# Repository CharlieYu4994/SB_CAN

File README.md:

# SB_CAN (StealthBurner_CAN)
为 Voron Design 的 StealthBurner 设计的工具头 PCB 板

## 特点
+ 使用 StealthBurner 官方的固定孔位，可以无损兼容现有打印件
+ 使用 CAN 总线与主控制器通讯，可靠性更好
+ 板载 ADXL345，无需另外安装加速度计就可以做共振补偿
+ 板载 MAX31865，可以使用二/三/四线制 PT100 温度传感器
+ 板载 TMP235，可以做仓温监控
+ 板载三路四线风扇接口，可以监控风扇转速
+ 预留线性霍尔提供耗材直径检测
+ 预留一路 I2C 接口，可以使用 LDC1612 IDM 传感器

## 使用

### 打样
使用各文件夹内的「SB-**-board.zip」文件即可，建议使用 1.6mm 板厚，4mil 最小线宽

### 接线 (均为从左向右)

+ FAN2 (风扇2)
  + +24V
  + GPIO14
  + GPIO15
  + GND
+ FS (耗材传感器)
  + +3.3V
  + GPI16
  + ADC0
  + GND
+ LDC (LDC1612)
  + GND
  + GPIO8
  + GPIO7
  + +5V
+ PT100
  + FORCE-
  + RTDIN-
  + RTDIN+
  + FORCE+
+ HS (上下)
  + GND (GPIO17)
  + +24V

+ STEP (步进电机)
  + A-
  + A+
  + B+
  + B-

+ FAN1 (风扇1)
  + +12V
  + GPIO13
  + GPIO11
  + GND
+ NEO (WS2812 LED)
  + GND
  + GPIO9
  + +3.7V
+ FAN0 (风扇0)
  + GND
  + GPIO12
  + GPIO10
  + +12V

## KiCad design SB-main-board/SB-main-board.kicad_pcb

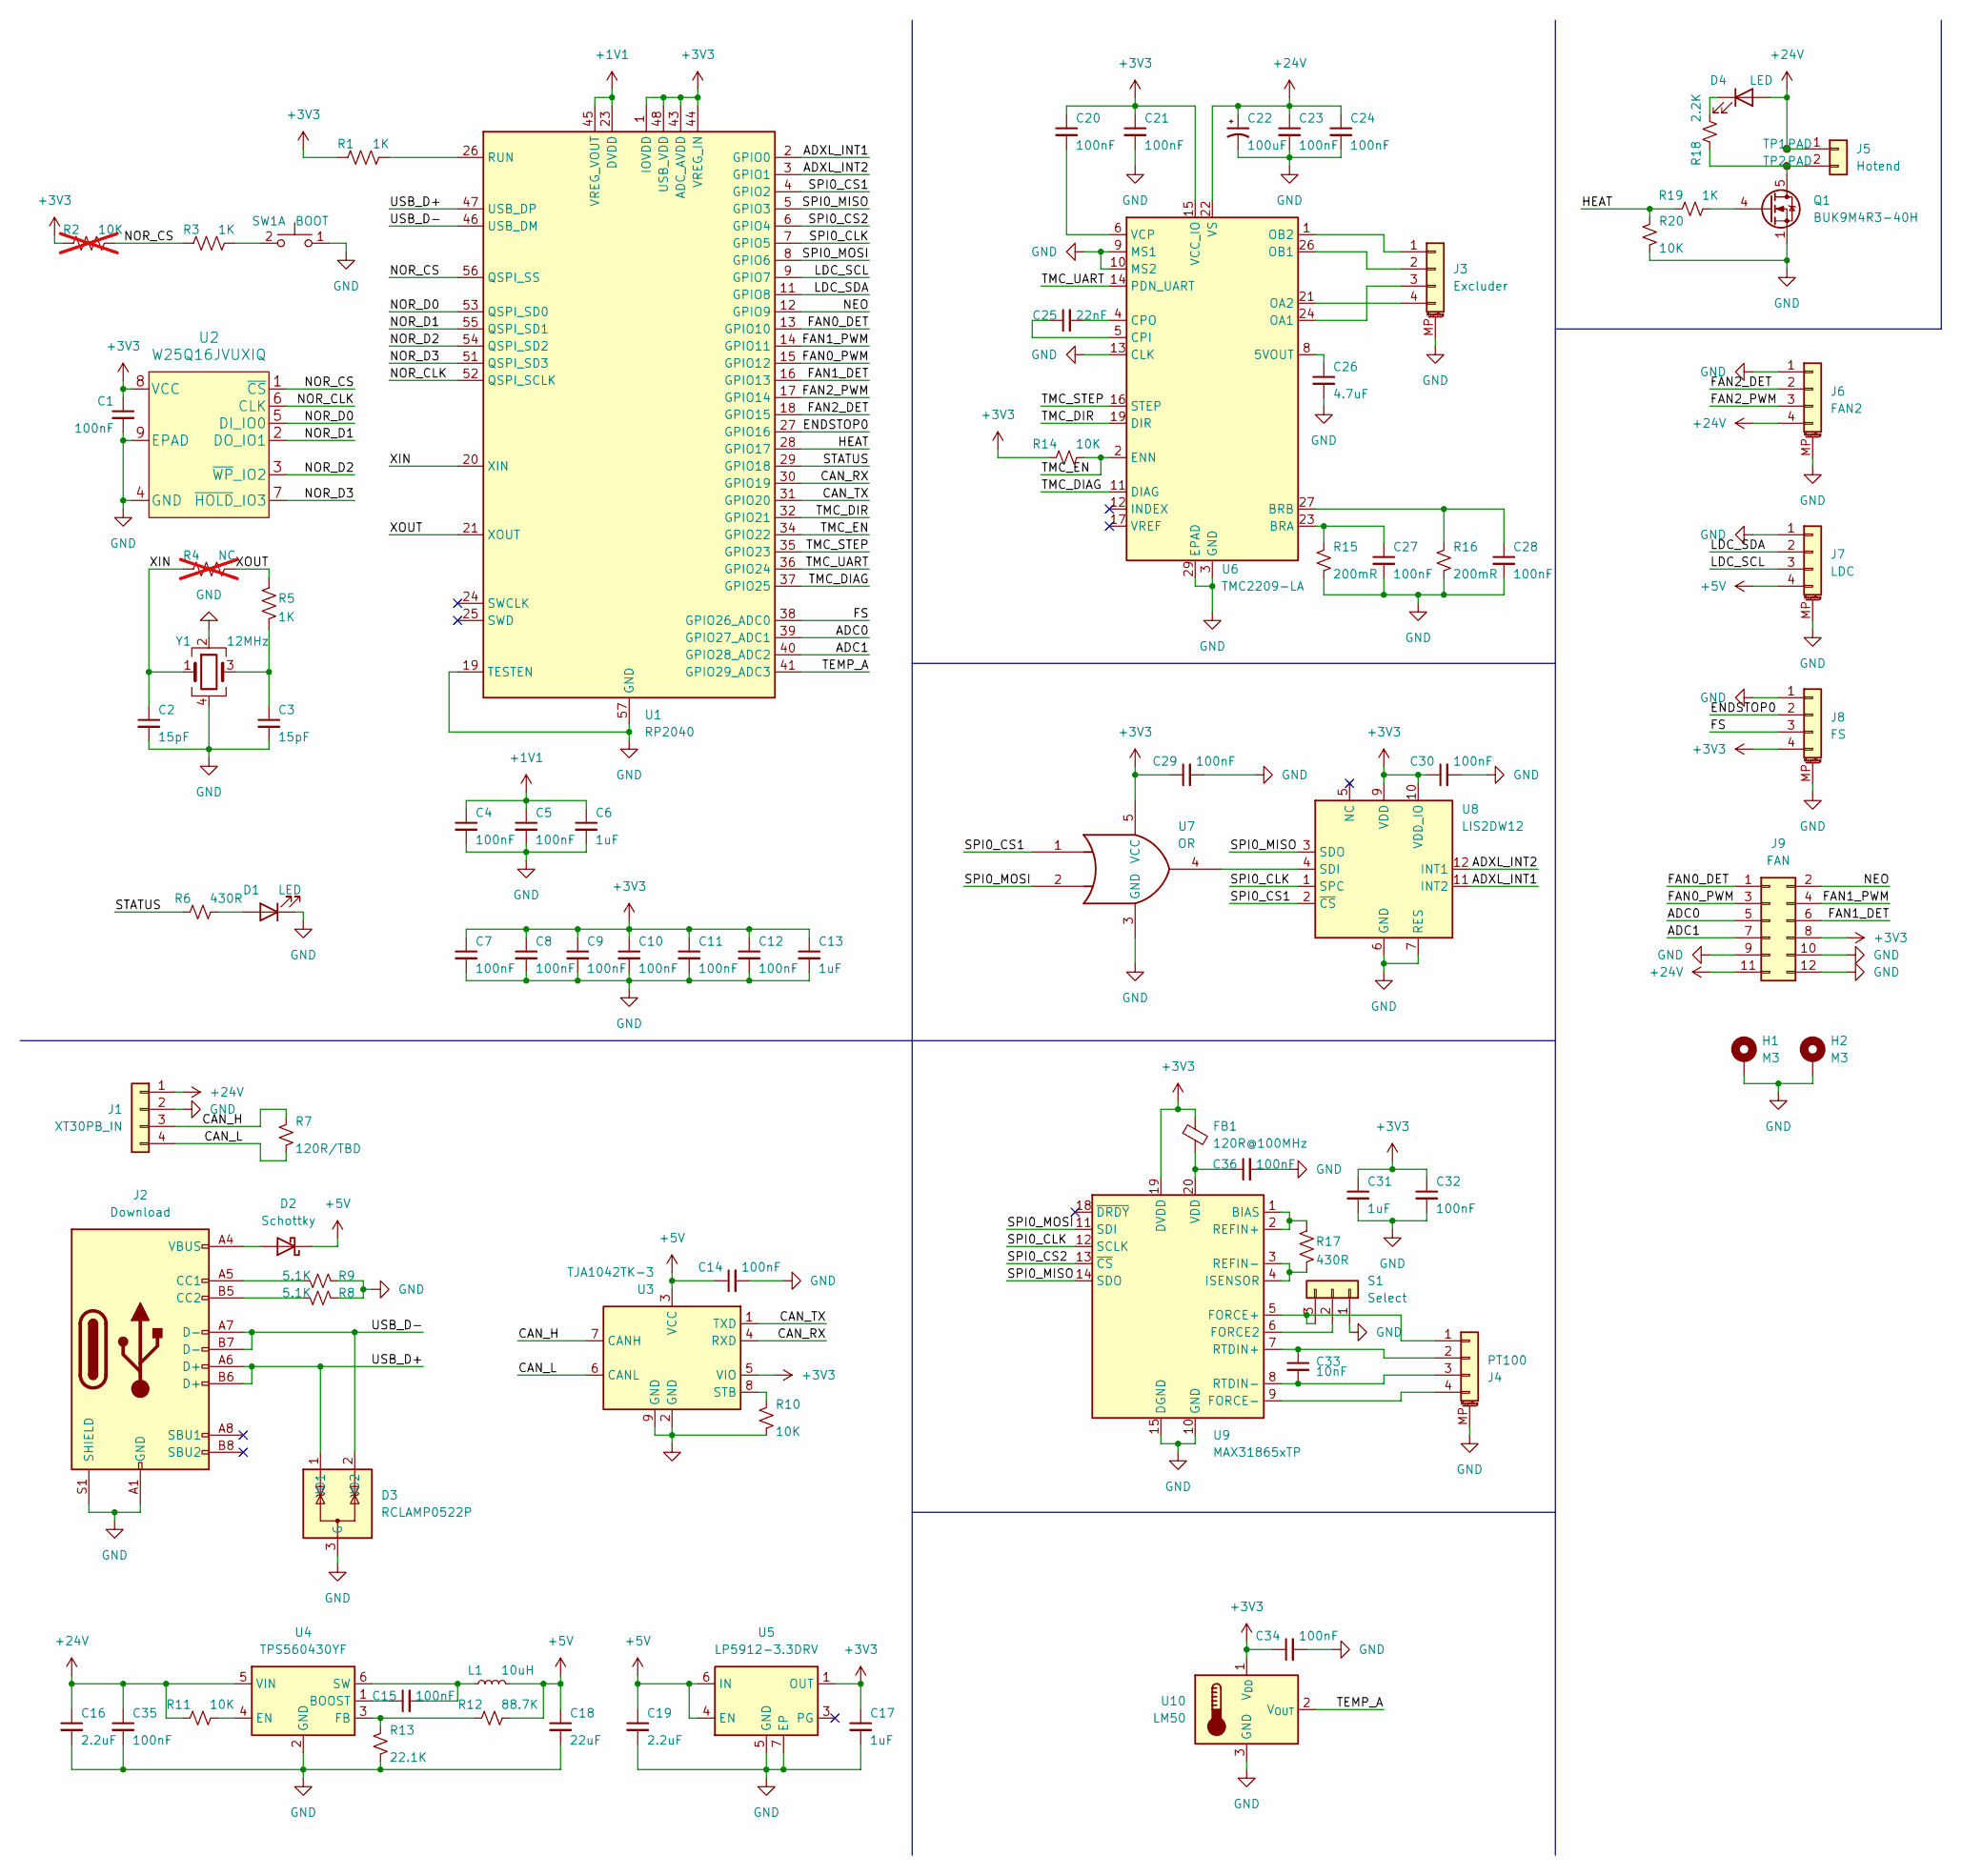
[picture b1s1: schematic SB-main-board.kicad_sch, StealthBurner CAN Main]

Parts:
C1, C4, C5, C7, C8, C9, C10, C11, C12, C14, C15, C20, C21, C23, C24, C27, C28, C29, C30, C32, C34, C35, C36: 100nF; C_0402_1005Metric
C2, C3: 15pF; C_0402_1005Metric
C6, C13, C31: 1uF; C_0402_1005Metric
C16: 2.2uF; C_1206_3216Metric
C17: 1uF; C_0603_1608Metric
C18: 22uF; C_0805_2012Metric
C19: 2.2uF; C_0603_1608Metric
C22: 100uF; CP_Elec_6.3x7.7
C25: 22nF; C_0402_1005Metric
C26: 4.7uF; C_0805_2012Metric
C33: 10nF; C_0402_1005Metric
D1, D4: LED; LED_0402_1005Metric
D2: Schottky; D_SOD-882D
D3: RCLAMP0522P; SLP1610P4
FB1: 120R@100MHz; L_0603_1608Metric
H1, H2: M3; MountingHole_3.2mm_M3_ISO14580_Pad
J1: XT30PB_IN; AMASS_XT30PW-M_1x02_P2.50mm_Horizontal
J2: Download; USB_C_Receptacle_GCT_USB4105-xx-A_16P_TopMnt_Horizontal
J3: Excluder; JST_PH_B4B-PH-SM4-TB_1x04-1MP_P2.00mm_Vertical
J4: PT100; Molex_PicoBlade_53261-0471_1x04-1MP_P1.25mm_Horizontal
J5: Hotend; Molex_Micro-Fit_3.0_43045-0200_2x01_P3.00mm_Horizontal
J6: FAN2; Molex_PicoBlade_53398-0471_1x04-1MP_P1.25mm_Vertical
J7: LDC; Molex_PicoBlade_53261-0471_1x04-1MP_P1.25mm_Horizontal
J8: FS; Molex_PicoBlade_53398-0471_1x04-1MP_P1.25mm_Vertical
J9: FAN; PinHeader_2x06_P2.00mm_Horizontal
L1: 10uH; L_Changjiang_FTC303020D
Q1: BUK9M4R3-40H; LFPAK33
R1, R3, R5, R19: 1K; R_0402_1005Metric
R2: 10K; R_0402_1005Metric; not fitted
R4: NC; R_0402_1005Metric; not fitted
R6: 430R; R_0402_1005Metric
R7: 120R/TBD; R_0805_2012Metric
R8, R9: 5.1K; R_0402_1005Metric
R10, R11, R14, R20: 10K; R_0402_1005Metric
R12: 88.7K; R_0402_1005Metric
R13: 22.1K; R_0402_1005Metric
R15, R16: 200mR; R_0805_2012Metric
R17: 430R; R_0603_1608Metric
R18: 2.2K; R_0402_1005Metric
S1: Select
SW1: BOOT; Panasonic_EVQPUJ_EVQPUA
TP1, TP2: PAD
U1: RP2040; QFN-56-1EP_7x7mm_P0.4mm_EP3.2x3.2mm
U2: W25Q16JVUXIQ; USON-8_2.0x3.0mm_P0.5mm
U3: TJA1042TK-3; DFN-8-1EP_3x3mm_P0.65mm_EP1.55x2.4mm
U4: TPS560430YF; SOT-23-6
U5: LP5912-3.3DRV; WSON-6-1EP_2x2mm_P0.65mm_EP1x1.6mm
U6: TMC2209-LA; QFN-28-1EP_5x5mm_P0.5mm_EP3.75x3.75mm
U7: OR; SOT-353_SC-70-5
U8: LIS2DW12; LGA-12_2x2mm_P0.5mm
U9: MAX31865xTP; TQFN-20-1EP_5x5mm_P0.65mm_EP3.25x3.25mm
U10: LM50; SOT-23
Y1: 12MHz; Crystal_SMD_2520-4Pin_2.5x2.0mm

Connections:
+1V1: C4.1, C5.1, C6.1, U1.23 (DVDD), U1.45 (VREG_VOUT), U1.50 (DVDD)
+3V3: C1.1, C7.1, C8.1, C9.1, C10.1, C11.1, C12.1, C13.1, C17.1, C20.1, C21.1, C29.1, C30.1, C31.1, C32.1, C34.1, FB1.1, J8.4, J9.8, R1.1, R2.1, R14.1, U1.1 (IOVDD), U1.10 (IOVDD), U1.22 (IOVDD), U1.33 (IOVDD), U1.42 (IOVDD), U1.43 (ADC_AVDD), U1.44 (VREG_IN), U1.48 (USB_VDD), U1.49 (IOVDD), U2.8 (VCC), U3.5 (VIO), U5.1 (OUT), U6.15 (VCC_IO), U7.5 (VCC), U8.9 (VDD), U8.10 (VDD_IO), U9.19 (DVDD), U10.1 (V_{DD})
+5V: C14.1, C18.1, C19.1, D2.1 (K), J7.4, L1.2, R12.2, U3.3 (VCC), U5.4 (EN), U5.6 (IN)
+24V: C16.1, C22.1, C23.1, C24.1, C35.1, D4.2 (A), J1.1, J5.1, J6.4, J9.11, R11.1, TP1.1, U4.5 (VIN), U6.22 (VS), U6.28 (VS)
/ADC0: J9.5, U1.39 (GPIO27_ADC1)
/ADC1: J9.7, U1.40 (GPIO28_ADC2)
/ADXL_INT1: U1.2 (GPIO0), U8.11 (INT2)
/ADXL_INT2: U1.3 (GPIO1), U8.12 (INT1)
/CAN_H: J1.3, R7.1, U3.7 (CANH)
/CAN_L: J1.4, R7.2, U3.6 (CANL)
/CAN_RX: U1.30 (GPIO19), U3.4 (RXD)
/CAN_TX: U1.31 (GPIO20), U3.1 (TXD)
/ENDSTOP0: J8.2, U1.27 (GPIO16)
/FAN0_DET: J9.1, U1.13 (GPIO10)
/FAN0_PWM: J9.3, U1.15 (GPIO12)
/FAN1_DET: J9.6, U1.16 (GPIO13)
/FAN1_PWM: J9.4, U1.14 (GPIO11)
/FAN2_DET: J6.2, U1.18 (GPIO15)
/FAN2_PWM: J6.3, U1.17 (GPIO14)
/FS: J8.3, U1.38 (GPIO26_ADC0)
/HEAT: R19.1, R20.1, U1.28 (GPIO17)
/LDC_SCL: J7.3, U1.9 (GPIO7)
/LDC_SDA: J7.2, U1.11 (GPIO8)
/NEO: J9.2, U1.12 (GPIO9)
/NOR_CLK: U1.52 (QSPI_SCLK), U2.6 (CLK)
/NOR_CS: R2.2, R3.1, U1.56 (QSPI_SS), U2.1 (~CS)
/NOR_D0: U1.53 (QSPI_SD0), U2.5 (DI_IO0)
/NOR_D1: U1.55 (QSPI_SD1), U2.2 (DO_IO1)
/NOR_D2: U1.54 (QSPI_SD2), U2.3 (~WP_IO2)
/NOR_D3: U1.51 (QSPI_SD3), U2.7 (~HOLD_IO3)
/SPI0_CLK: U1.7 (GPIO5), U8.1 (SPC), U9.12 (SCLK)
/SPI0_CS1: U1.4 (GPIO2), U7.1, U8.2 (~CS)
/SPI0_CS2: U1.6 (GPIO4), U9.13 (~CS)
/SPI0_MISO: U1.5 (GPIO3), U8.3 (SDO), U9.14 (SDO)
/SPI0_MOSI: U1.8 (GPIO6), U7.2, U9.11 (SDI)
/STATUS: R6.1, U1.29 (GPIO18)
/TEMP_A: U1.41 (GPIO29_ADC3), U10.2 (V_{OUT})
/TMC_DIAG: U1.37 (GPIO25), U6.11 (DIAG)
/TMC_DIR: U1.32 (GPIO21), U6.19 (DIR)
/TMC_EN: R14.2, U1.34 (GPIO22), U6.2 (ENN)
/TMC_STEP: U1.35 (GPIO23), U6.16 (STEP)
/TMC_UART: U1.36 (GPIO24), U6.14 (PDN_UART)
/USB_D+: D3.1 (IO1), D3.6 (NC), J2.A6 (D+), J2.B6 (D+), U1.47 (USB_DP)
/USB_D-: D3.2 (IO2), D3.5 (NC), J2.A7 (D-), J2.B7 (D-), U1.46 (USB_DM)
/XIN: C2.1, R4.1, U1.20 (XIN), Y1.1
/XOUT: R4.2, R5.2, U1.21 (XOUT)
GND: C1.2, C2.2, C3.2, C4.2, C5.2, C6.2, C7.2, C8.2, C9.2, C10.2, C11.2, C12.2, C13.2, C14.2, C16.2, C17.2, C18.2, C19.2, C21.2, C22.2, C23.2, C24.2, C26.2, C27.2, C28.2, C29.2, C30.2, C31.2, C32.2, C34.2, C35.2, C36.2, D1.1 (K), D3.3 (G), D3.4 (G), H1.1, H2.1, J1.2, J2.A1 (GND), J2.A12 (GND), J2.B1 (GND), J2.B12 (GND), J2.S1 (SHIELD), J3.MP (MountPin), J4.MP (MountPin), J6.1, J6.MP (MountPin), J7.1, J7.MP (MountPin), J8.1, J8.MP (MountPin), J9.9, J9.10, J9.12, Q1.1 (S), Q1.2 (S), Q1.3 (S), R8.1, R9.1, R10.2, R13.2, R15.2, R16.2, R20.2, S1.1, SW1.1 (C), U1.19 (TESTEN), U1.57 (GND), U2.4 (GND), U2.9 (EPAD), U3.2 (GND), U3.9 (GND), U4.2 (GND), U5.5 (GND), U5.7 (EP), U6.3 (GND), U6.9 (MS1), U6.10 (MS2), U6.13 (CLK), U6.18 (GND), U6.29 (EPAD), U7.3 (GND), U8.6 (GND), U8.7 (RES), U8.8 (GND), U9.10 (GND), U9.15 (DGND), U9.16 (GND), U9.21 (GND), U10.3 (GND), Y1.2, Y1.4
unnamed: C3.1, R5.1, Y1.3
unnamed: D1.2 (A), R6.2
unnamed: D2.2 (A), J2.A4 (VBUS), J2.A9 (VBUS), J2.B4 (VBUS), J2.B9 (VBUS)
unnamed: D4.1 (K), R18.2
unnamed: J2.A5 (CC1), R9.2
unnamed: J2.B5 (CC2), R8.2
unnamed: J3.1, U6.1 (OB2)
unnamed: J3.2, U6.26 (OB1)
unnamed: J3.3, U6.24 (OA1)
unnamed: J3.4, U6.21 (OA2)
unnamed: J4.1, S1.3, U9.5 (FORCE+)
unnamed: C33.1, J4.2, U9.7 (RTDIN+)
unnamed: C33.2, J4.3, U9.8 (RTDIN-)
unnamed: J4.4, U9.9 (FORCE-)
unnamed: J5.2, Q1.5 (D), R18.1, TP2.1
unnamed: Q1.4 (G), R19.2
unnamed: S1.2, U9.6 (FORCE2)
unnamed: R3.2, SW1.2 (D)
unnamed: R1.2, U1.26 (RUN)
unnamed: R10.1, U3.8 (STB)
unnamed: C15.1, U4.1 (BOOST)
unnamed: R11.2, U4.4 (EN)
unnamed: R12.1, R13.1, U4.3 (FB)
unnamed: C15.2, L1.1, U4.6 (SW)
unnamed: C26.1, U6.8 (5VOUT)
unnamed: C27.1, R15.1, U6.23 (BRA)
unnamed: C28.1, R16.1, U6.27 (BRB)
unnamed: C25.1, U6.5 (CPI)
unnamed: C25.2, U6.4 (CPO)
unnamed: C20.2, U6.6 (VCP)
unnamed: U7.4, U8.4 (SDI)
unnamed: R17.2, U9.1 (BIAS), U9.2 (REFIN+)
unnamed: R17.1, U9.3 (REFIN-), U9.4 (ISENSOR)
unnamed: C36.1, FB1.2, U9.20 (VDD)

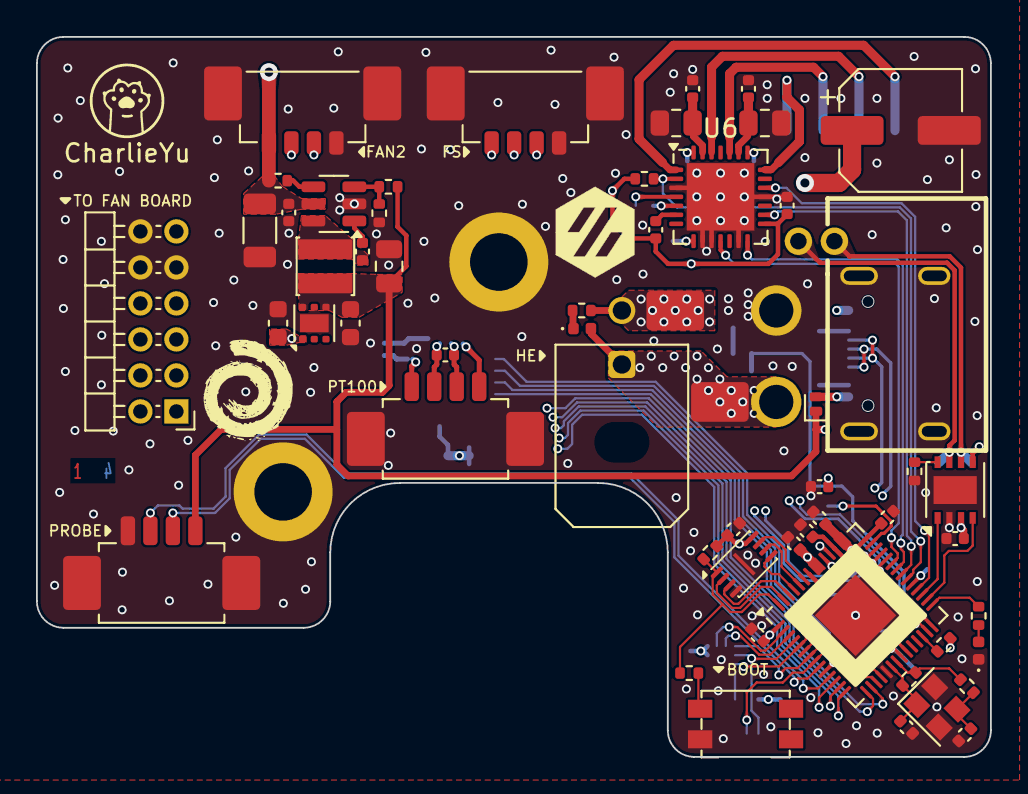
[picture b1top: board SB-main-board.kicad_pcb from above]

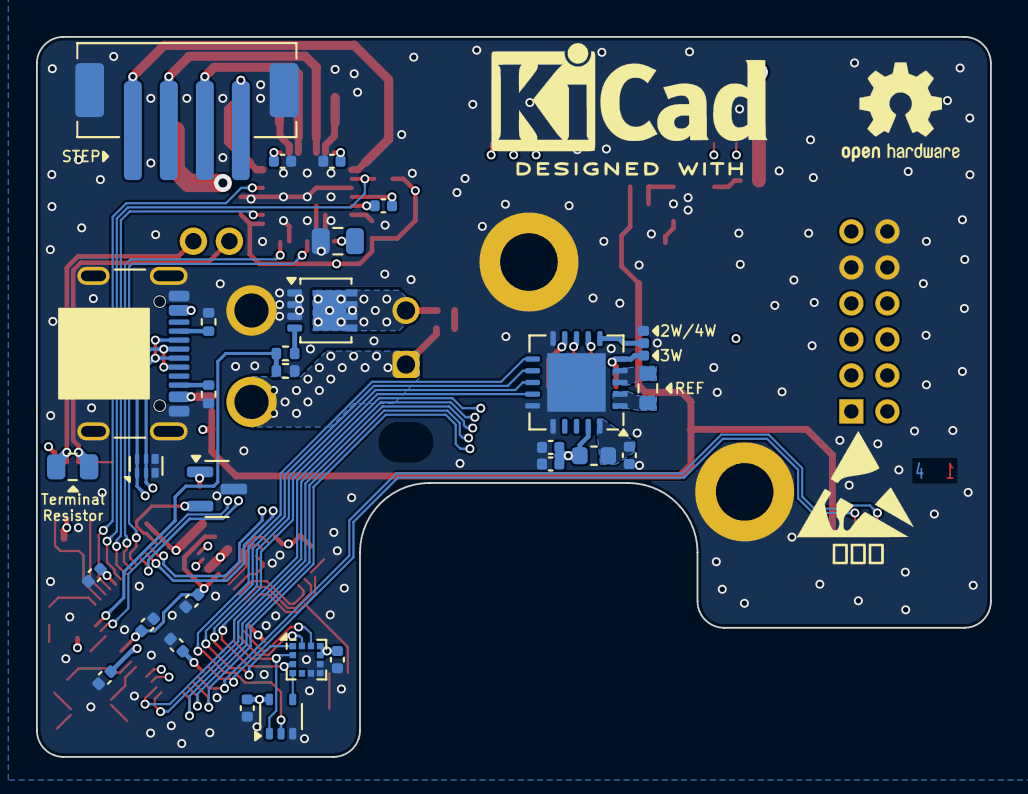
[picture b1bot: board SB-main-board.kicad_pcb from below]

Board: 4 copper layers, 53.0 x 40.0 mm, 95 parts (33 on the bottom side), 81 nets.

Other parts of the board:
G1: CharlieYu; charlieyu
G2: LOGO; Progynova
G3: Voron Hex; Voron_Logo_Hex
G4: KiCad-Logo2_6mm_SilkScreen
G5: OSHW-Logo2_7.3x6mm_SilkScreen
G6: ESD-Logo_6.6x6mm_SilkScreen

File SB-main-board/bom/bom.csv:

"Reference","Value","Footprint","Qty","DNP"
"C2,C3","15pF","Capacitor_SMD:C_0402_1005Metric","2",""
"C33","10nF","Capacitor_SMD:C_0402_1005Metric","1",""
"C25","22nF","Capacitor_SMD:C_0402_1005Metric","1",""
"C1,C4,C5,C7,C8,C9,C10,C11,C12,C14,C15,C20,C21,C23,C24,C27,C28,C29,C30,C32,C34,C35,C36","100nF","Capacitor_SMD:C_0402_1005Metric","23",""
"C6,C13,C31","1uF","Capacitor_SMD:C_0402_1005Metric","3",""
"C17","1uF","Capacitor_SMD:C_0603_1608Metric","1",""
"C16","2.2uF","Capacitor_SMD:C_1206_3216Metric","1",""
"C19","2.2uF","Capacitor_SMD:C_0603_1608Metric","1",""
"C26","4.7uF","Capacitor_SMD:C_0805_2012Metric","1",""
"L1","10uH","Library:L_Changjiang_FTC303020D","1",""
"C18","22uF","Capacitor_SMD:C_0805_2012Metric","1",""
"C22","100uF","Capacitor_SMD:CP_Elec_6.3x7.7","1",""
"R7","120R/TBD","Resistor_SMD:R_0805_2012Metric","1",""
"R15,R16","200mR","Resistor_SMD:R_0805_2012Metric","2",""
"R6","430R","Resistor_SMD:R_0402_1005Metric","1",""
"R17","430R","Resistor_SMD:R_0603_1608Metric","1",""
"R1,R3,R5,R19","1K","Resistor_SMD:R_0402_1005Metric","4",""
"R18","2.2K","Resistor_SMD:R_0402_1005Metric","1",""
"R8,R9","5.1K","Resistor_SMD:R_0402_1005Metric","2",""
"R2","10K","Resistor_SMD:R_0402_1005Metric","1","DNP (不作装配)"
"R10,R11,R14,R20","10K","Resistor_SMD:R_0402_1005Metric","4",""
"R13","22.1K","Resistor_SMD:R_0402_1005Metric","1",""
"R12","88.7K","Resistor_SMD:R_0402_1005Metric","1",""
"Y1","12MHz","Crystal:Crystal_SMD_2520-4Pin_2.5x2.0mm","1",""
"FB1","120R@100MHz","Inductor_SMD:L_0603_1608Metric","1",""
"SW1","BOOT","Library:Panasonic_EVQPUJ_EVQPUA","1",""
"Q1","BUK9M4R3-40H","Package_TO_SOT_SMD:LFPAK33","1",""
"J2","Download","Connector_USB:USB_C_Receptacle_GCT_USB4105-xx-A_16P_TopMnt_Horizontal","1",""
"J3","Excluder","Library:JST_PH_B4B-PH-SM4-TB_1x04-1MP_P2.00mm_Vertical","1",""
"J9","FAN","Library:PinHeader_2x06_P2.00mm_Horizontal","1",""
"J6","FAN2","Library:Molex_PicoBlade_53398-0471_1x04-1MP_P1.25mm_Vertical","1",""
"J8","FS","Library:Molex_PicoBlade_53398-0471_1x04-1MP_P1.25mm_Vertical","1",""
"J5","Hotend","Library:Molex_Micro-Fit_3.0_43045-0200_2x01_P3.00mm_Horizontal","1",""
"J7","LDC","Library:Molex_PicoBlade_53261-0471_1x04-1MP_P1.25mm_Horizontal","1",""
"D1,D4","LED","LED_SMD:LED_0402_1005Metric","2",""
"U8","LIS2DW12","Package_LGA:LGA-12_2x2mm_P0.5mm","1",""
"U10","LM50","Package_TO_SOT_SMD:SOT-23","1",""
"U5","LP5912-3.3DRV","Package_SON:WSON-6-1EP_2x2mm_P0.65mm_EP1x1.6mm","1",""
"U9","MAX31865xTP","Package_DFN_QFN:TQFN-20-1EP_5x5mm_P0.65mm_EP3.25x3.25mm","1",""
"R4","NC","Resistor_SMD:R_0402_1005Metric","1","DNP (不作装配)"
"U7","OR","Package_TO_SOT_SMD:SOT-353_SC-70-5","1",""
"TP1,TP2","PAD","Library:PAD","2",""
"J4","PT100","Library:Molex_PicoBlade_53261-0471_1x04-1MP_P1.25mm_Horizontal","1",""
"D3","RCLAMP0522P","Library:SLP1610P4","1",""
"U1","RP2040","Package_DFN_QFN:QFN-56-1EP_7x7mm_P0.4mm_EP3.2x3.2mm","1",""
"D2","Schottky","Diode_SMD:D_SOD-882D","1",""
"S1","Select","Library:Select","1",""
"U3","TJA1042TK-3","Package_DFN_QFN:DFN-8-1EP_3x3mm_P0.65mm_EP1.55x2.4mm","1",""
"U6","TMC2209-LA","Package_DFN_QFN:QFN-28-1EP_5x5mm_P0.5mm_EP3.75x3.75mm","1",""
"U4","TPS560430YF","Package_TO_SOT_SMD:SOT-23-6","1",""
"U2","W25Q16JVUXIQ","Library:USON-8_2.0x3.0mm_P0.5mm","1",""
"J1","XT30PB_IN","Library:AMASS_XT30PW-M_1x02_P2.50mm_Horizontal","1",""

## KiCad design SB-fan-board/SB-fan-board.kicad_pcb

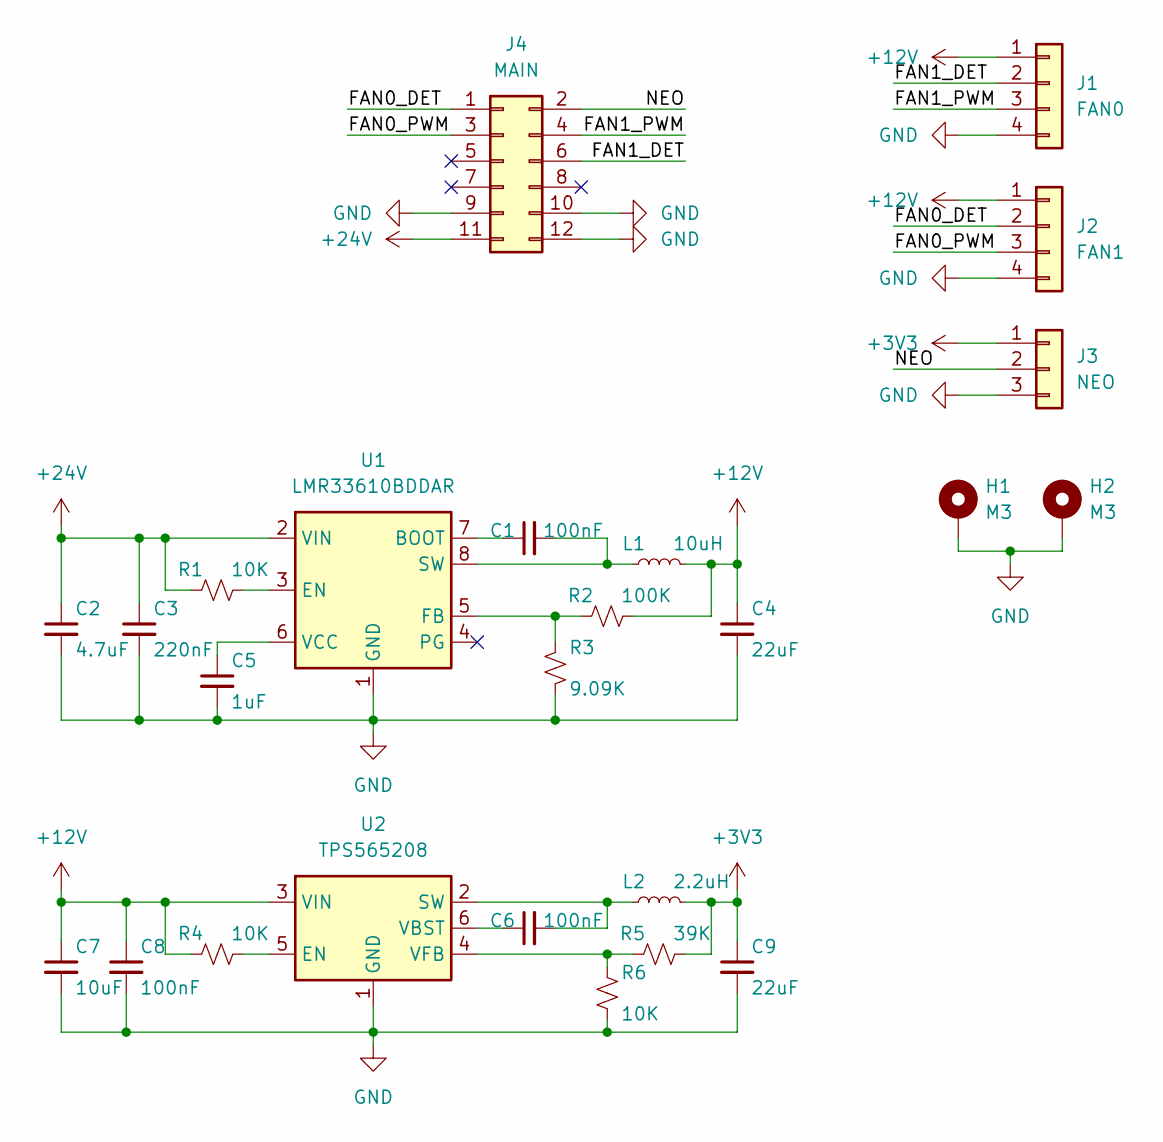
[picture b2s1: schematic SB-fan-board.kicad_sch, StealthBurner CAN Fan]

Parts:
C1, C6, C8: 100nF; C_0603_1608Metric
C2: 4.7uF; C_1206_3216Metric
C3: 220nF; C_0603_1608Metric
C4, C9: 22uF; C_0805_2012Metric
C5: 1uF; C_0603_1608Metric
C7: 10uF; C_0805_2012Metric
H1, H2: M3; MountingHole_3.2mm_M3_ISO14580_Pad
J1: FAN0; JST_PH_B4B-PH-K_1x04_P2.00mm_SMD
J2: FAN1; JST_PH_B4B-PH-K_1x04_P2.00mm_SMD
J3: NEO; JST_PH_B3B-PH-K_1x03_P2.00mm_SMD
J4: MAIN; PinSocket_2x06_P2.00mm_Vertical_SMD
L1: 10uH; L_Sunlord_SWPA4030S
L2: 2.2uH; L_Murata_DFE201610P
R1, R4, R6: 10K; R_0603_1608Metric
R2: 100K; R_0603_1608Metric
R3: 9.09K; R_0603_1608Metric
R5: 39K; R_0603_1608Metric
U1: LMR33610BDDAR; Texas_HSOP-8-1EP_3.9x4.9mm_P1.27mm
U2: TPS565208; SOT-23-6

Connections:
+3V3: C9.1, J3.1, L2.2, R5.2
+12V: C4.1, C7.1, C8.1, J1.1, J2.1, L1.2, R2.2, R4.1, U2.3 (VIN)
+24V: C2.1, C3.1, J4.11, R1.1, U1.2 (VIN)
/FAN0_DET: J2.2, J4.1
/FAN0_PWM: J2.3, J4.3
/FAN1_DET: J1.2, J4.6
/FAN1_PWM: J1.3, J4.4
/NEO: J3.2, J4.2
GND: C2.2, C3.2, C4.2, C5.2, C7.2, C8.2, C9.2, H1.1, H2.1, J1.4, J2.4, J3.3, J4.9, J4.10, J4.12, R3.2, R6.2, U1.1 (GND), U1.9 (GND), U2.1 (GND)
unnamed: C1.1, U1.7 (BOOT)
unnamed: R1.2, U1.3 (EN)
unnamed: R2.1, R3.1, U1.5 (FB)
unnamed: C1.2, L1.1, U1.8 (SW)
unnamed: C5.1, U1.6 (VCC)
unnamed: R4.2, U2.5 (EN)
unnamed: C6.2, L2.1, U2.2 (SW)
unnamed: C6.1, U2.6 (VBST)
unnamed: R5.1, R6.1, U2.4 (VFB)

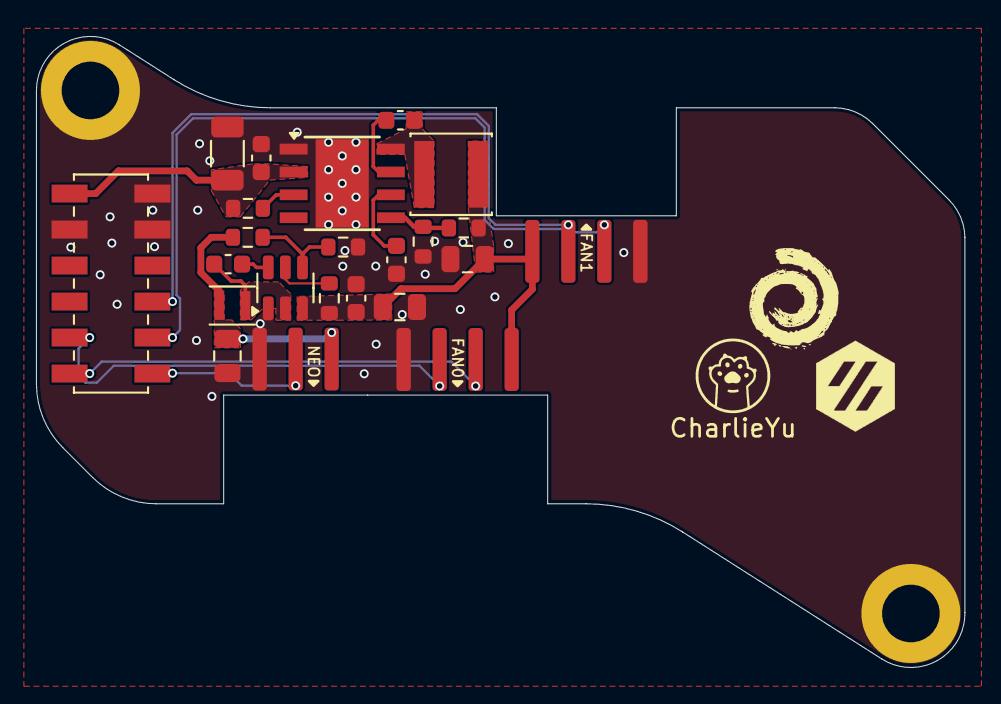
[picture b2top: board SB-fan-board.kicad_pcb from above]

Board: 2 copper layers, 51.6 x 35.1 mm, 26 parts (0 on the bottom side), 18 nets.

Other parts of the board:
RFF**: CharlieYu; charlieyu

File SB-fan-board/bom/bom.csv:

"Reference","Value","Datasheet","Footprint","Qty","DNP"
"C1,C6,C8","100nF","~","Capacitor_SMD:C_0603_1608Metric","3",""
"C2","4.7uF","~","Capacitor_SMD:C_1206_3216Metric","1",""
"C3","220nF","~","Capacitor_SMD:C_0603_1608Metric","1",""
"C4,C9","22uF","~","Capacitor_SMD:C_0805_2012Metric","2",""
"C5","1uF","~","Capacitor_SMD:C_0603_1608Metric","1",""
"C7","10uF","~","Capacitor_SMD:C_0805_2012Metric","1",""
"J1","FAN0","~","Library:JST_PH_B4B-PH-K_1x04_P2.00mm_SMD","1",""
"J2","FAN1","~","Library:JST_PH_B4B-PH-K_1x04_P2.00mm_SMD","1",""
"J3","NEO","~","Library:JST_PH_B3B-PH-K_1x03_P2.00mm_SMD","1",""
"J4","MAIN","~","Library:PinSocket_2x06_P2.00mm_Vertical_SMD","1",""
"L1","10uH","~","Inductor_SMD:L_Sunlord_SWPA4030S","1",""
"L2","2.2uH","~","Inductor_SMD:L_Murata_DFE201610P","1",""
"R1,R4,R6","10K","~","Resistor_SMD:R_0603_1608Metric","3",""
"R2","100K","~","Resistor_SMD:R_0603_1608Metric","1",""
"R3","9.09K","~","Resistor_SMD:R_0603_1608Metric","1",""
"R5","39K","~","Resistor_SMD:R_0603_1608Metric","1",""
"U1","LMR33610BDDAR","http://www.ti.com/lit/ds/symlink/lmr33610.pdf","Package_SO:Texas_HSOP-8-1EP_3.9x4.9mm_P1.27mm","1",""
"U2","TPS565208","http://www.ti.com/lit/ds/symlink/tps565208.pdf","Package_TO_SOT_SMD:SOT-23-6","1",""

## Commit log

2024-05-27 Init: initial upload
2024-05-27 source: delete unused files
2024-05-30 layout: optmise +3v3A power source: use new 3d models
2024-05-30 repo: ignore auto-generated files
2024-05-30 source: move files
2024-05-30 layout: add fan board
2024-05-30 source: ignore auto-generated files
2024-05-31 sch: fix bug that the tja1044 can only use 5V power
2024-05-31 source: rename the pcbs
2024-05-31 source: add readme
2024-05-31 mechanical: fix interference
2024-05-31 mechanical: optimise installation
2024-06-01 silkscreen: optmise silkscreen
2024-06-01 bugfix: use 5V for IDM sensor
2024-06-01 fab: generate gerbers and bom
2024-06-15 generate gerber files
2024-06-19 layout: optimise trace
2024-06-19 source: remove unused lib
2024-06-23 silkscreen: add more information
2024-06-25 sch: optimize return path
2024-06-25 fab: regenerate gerbers
2024-06-25 source: mask is now in gerber folder
2024-06-25 silkscreen: make silkscreen easy to read
2024-06-25 readme: update readme
2024-07-11 layout: optmise power layout
2024-12-10 update to v2
2024-12-10 3d: add more 3d modules
2024-12-11 sch: change accelerometer to LIS2DW12
2024-12-11 layout: change the accelerometer
2024-12-11 layout: optmise routes
2024-12-11 update fan board to v2
2024-12-12 generate manufacture files
2024-12-12 footprint: change the Micro-Fit 3.0 connector
2024-12-12 silkscreen: add silkscreen
2024-12-12 regenerate manufacture files
2024-12-12 sch: change the tvs to 0522
2024-12-12 layout: change the tvs to 0522
2024-12-15 change bom
2024-12-17 layout: delete unused area
2024-12-18 generate latest manufacture files
2024-12-19 layout: swap the led and the resistor
2024-12-19 layout: optime the routes for TMC2209
2024-12-19 3d: add missing module
2024-12-20 footprint: change input cap to 1206
2024-12-31 layout: optmise layout silkscreen: change silkscreen
2024-12-31 misc: fix typo
2024-12-31 misc: update bom
2025-01-01 layout: add rounded pcb
2025-02-23 misc: update to kicad 9
2025-02-23 misc: delete gerber
2025-02-23 action: test workflow
2025-02-23 action: bugfix
2025-02-23 action: fix permission
2025-02-23 action: fix kicad_cli error
2025-02-23 action: ready to use
2025-02-23 action: use posix shell only
2025-02-26 action: add workflow for gitea
2025-02-26 misc: update all files to kicad 9
2025-02-27 layout: update zone fills
2025-02-27 layout: change zone fill priority
2025-03-08 layout: add teardrops
